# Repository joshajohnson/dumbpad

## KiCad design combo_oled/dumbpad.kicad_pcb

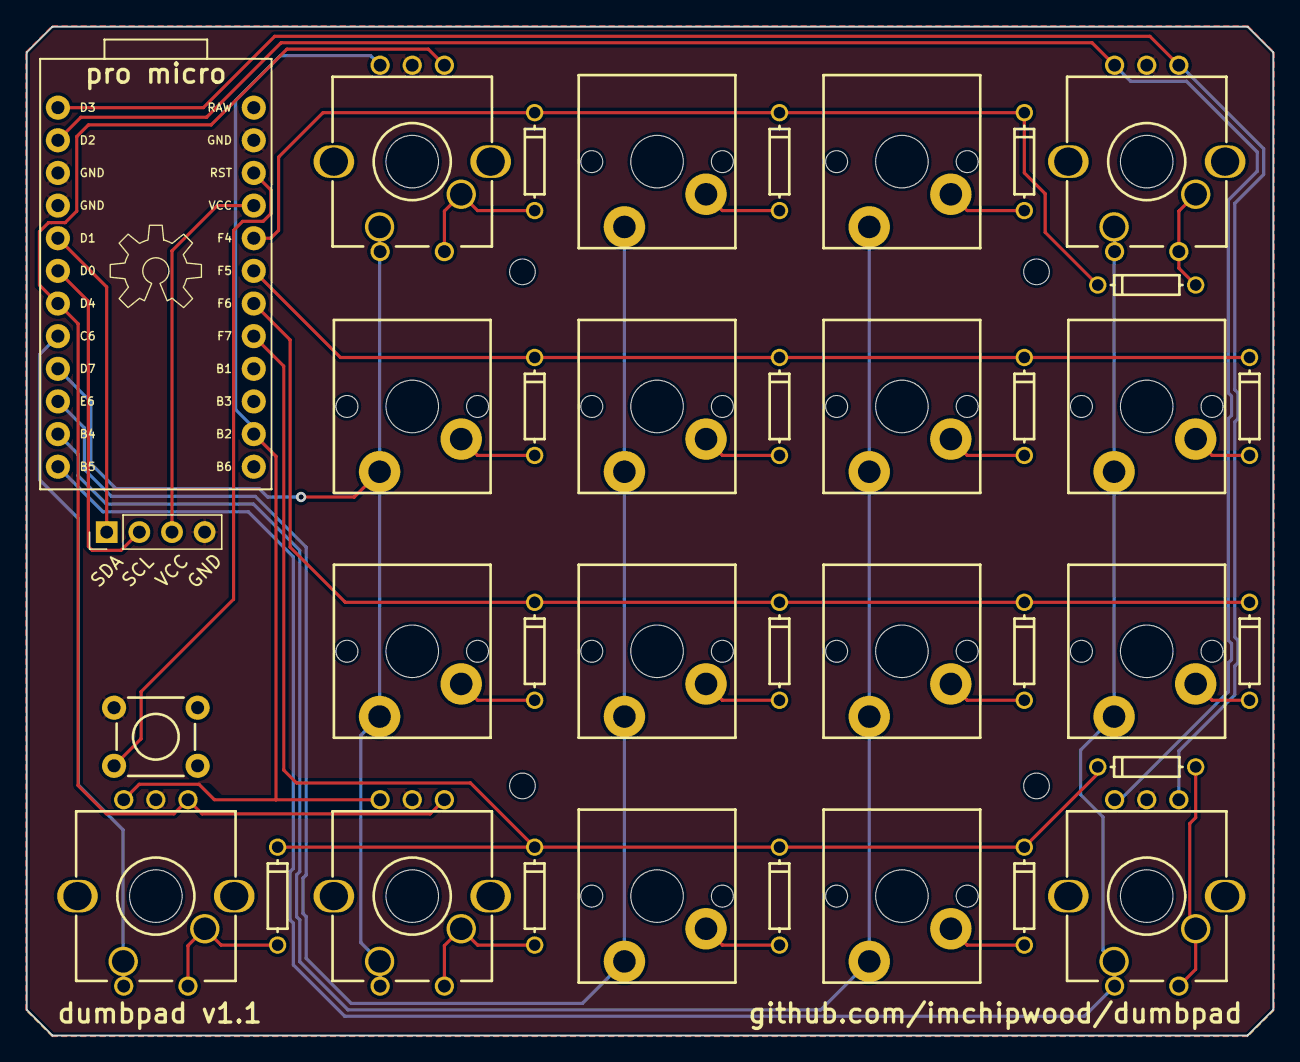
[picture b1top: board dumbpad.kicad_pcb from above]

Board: 2 copper layers, 97.0 x 78.5 mm, 43 parts (1 on the bottom side), 35 nets.

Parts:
@HOLE0, @HOLE1, @HOLE2, @HOLE3: (no value)
B1: SPARKFUN_PRO_MICRO
D1, D2, D3, D4, D5, D6, D7, D8, D9, D10, D11, D12, D13, D14, D15, D16, D20: DO-1N4148
JOLED1: Conn_01x04; PinHeader_1x04_P2.54mm_Vertical
LOGO1, LOGO2: OSHW-LOGOL; OSHW-LOGO-L
RE_0_1, RE_0_4, RE_3_0, RE_3_1, RE_3_4: Val**; CHERRY-MX-ENCODER
S2, S3, S5, S6, S7, S8, S9, S10, S11, S12, S14, S15: MOMENTARY-SWITCH-SPST-LED-PTH-CHERRY; CHERRY-MX-LED
S17: MOMENTARY-SWITCH-SPST-PTH-6.0MM; TACTILE_SWITCH_PTH_6.0MM

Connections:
COL0: B1.8, RE_3_0.E, RE_3_0.S2
COL1: B1.9, RE_0_1.E, RE_0_1.S2, RE_3_1.E, RE_3_1.S2, S5.S2, S9.S2
COL2: B1.10, S2.S2, S6.S2, S10.S2, S14.S2
COL3: B1.11, S3.S2, S7.S2, S11.S2, S15.S2
COL4: B1.12, RE_0_4.E, RE_0_4.S2, RE_3_4.E, RE_3_4.S2, S8.S2, S12.S2
ENCODER0_L0: B1.14, RE_0_1.B, RE_3_0.B, RE_3_1.B
ENCODER0_L1: B1.7, RE_0_1.A, RE_3_0.A, RE_3_1.A
ENCODER1_L0: B1.2, RE_0_4.B, RE_3_4.B
ENCODER1_L1: B1.1, RE_0_4.A, RE_3_4.A
GND: B1.3, B1.4, B1.23, JOLED1.4, RE_0_1.C, RE_0_4.C, RE_3_0.C, RE_3_1.C, RE_3_4.C, S17.1
unnamed: D4.A, RE_0_4.D, RE_0_4.S1
unnamed: D3.A, S3.S1
unnamed: D2.A, S2.S1
unnamed: D1.A, RE_0_1.D, RE_0_1.S1
unnamed: D8.A, S8.S1
unnamed: D7.A, S7.S1
unnamed: D6.A, S6.S1
unnamed: D5.A, S5.S1
unnamed: D16.A, RE_3_4.D, RE_3_4.S1
unnamed: D15.A, S15.S1
unnamed: D14.A, S14.S1
unnamed: D13.A, RE_3_1.D, RE_3_1.S1
unnamed: D12.A, S12.S1
unnamed: D11.A, S11.S1
unnamed: D10.A, S10.S1
unnamed: D9.A, S9.S1
unnamed: D20.A, RE_3_0.D, RE_3_0.S1
RESET: B1.22, S17.3
ROW0: B1.20, D1.C, D2.C, D3.C, D4.C
ROW1: B1.19, D5.C, D6.C, D7.C, D8.C
ROW2: B1.18, D9.C, D10.C, D11.C, D12.C
ROW3: B1.17, D13.C, D14.C, D15.C, D16.C, D20.C
SCL: B1.6, JOLED1.2
SDA: B1.5, JOLED1.1
VCC: B1.21, JOLED1.3

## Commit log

2022-01-22 add oled
